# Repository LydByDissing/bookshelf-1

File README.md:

# Bookshelf 1

This is a simply bookshelf speaker, based on a COAX driver from SB Acoustics. The cabinet are a bass reflex cabinet to increase the bass response.

## License
This project and all it's work are licensed under the [CERN Open Hardware Licence Version 2](https://ohwr.org/project/cernohl/wikis/Documents/CERN-OHL-version-2) license.

## Design goals

Initial design goals for this bookshelf speaker:

* Use a COAX driver for optimal timing between drivers
* Compact cabinet
* In room bass extention into the 40Hz range

## Current progress

Prototype cabinet have been designed and built. Initial measurements are been captured. Find them under the [measurements](measurements) folder.

Working on the finishing of the cabinet. Going with a painted finish and initially no driver cover.

An initial crossover have been designed, based on the captured measurements. I'm going for a 2nd order series filter. Currently it looks as depicted below.

The currently simulated results of the speaker + filter looks like this. This result will need to be confirmed by a measurement once the components have arrived.

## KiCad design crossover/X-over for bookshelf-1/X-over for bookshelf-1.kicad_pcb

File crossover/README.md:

# Crossover

The crossover have been simulated and modelled in XSim. The [XSim project file](2-way_LR_eries.dxo) contains the filter simulation.
The measurements used doesn't include impendance measurements.

We are going for a crossover frequence of around 2500Hz. This to keep a reasonable wide dispersion.

As seen in the driver measurements the bass driver has various issues above the crossover frequency wich require us to ensure that these are lowered enough, to not make an audible impact in the tweeter section.

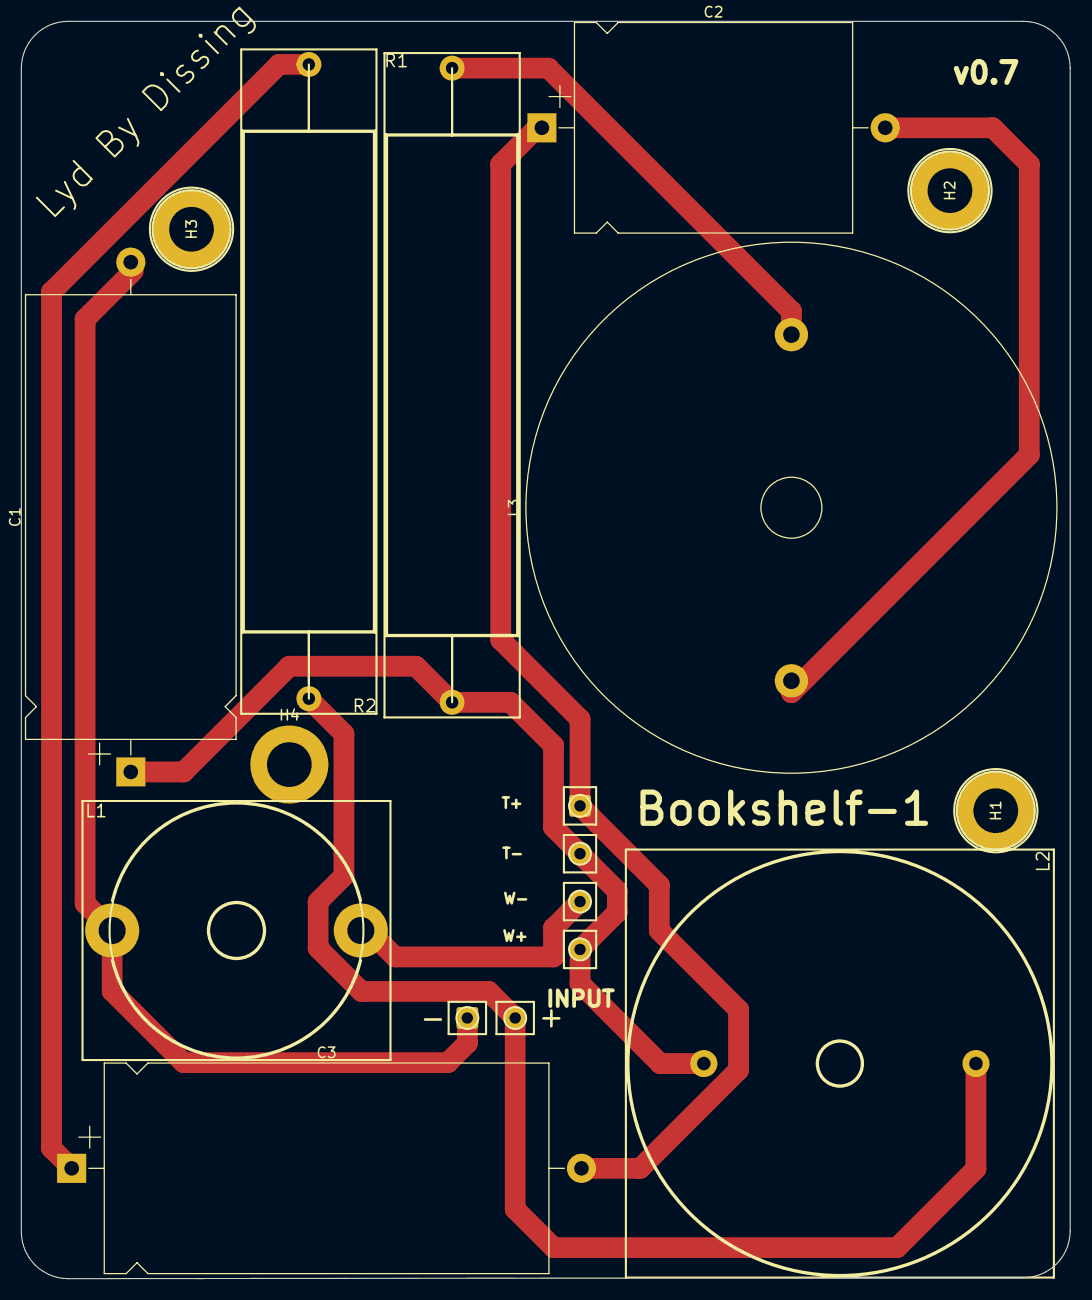
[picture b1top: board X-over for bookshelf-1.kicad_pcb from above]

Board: 2 copper layers, 100.8 x 120.9 mm, 14 parts (0 on the bottom side), 8 nets.

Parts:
C1: 12µF; CP_Axial_L42.5mm_D20.0mm_P49.00mm_Horizontal
C2: 47µF; CP_Axial_L26.5mm_D20.0mm_P33.00mm_Horizontal
C3: 8µF; CP_Axial_L42.5mm_D20.0mm_P49.00mm_Horizontal
H1, H2, H3, H4: MountingHole; MountingHole_4.3mm_M4_DIN965_Pad
J1: Input; SolderWire-0.5sqmm_1x02_P4.6mm_D0.9mm_OD2.1mm
J2: Output; SolderWire-0.5sqmm_1x04_P4.6mm_D0.9mm_OD2.1mm
L1: 1,5mH; L_Radial_D24.4mm_P23.90mm_Murata_1400series
L2: 0,22mH; L_Radial_D40.6mm_P26.16mm_Vishay_IHB-5
L3: 0.1mH; L_Radial_D50.8mm_P33.27mm_Vishay_IHB-6
R1: 1.8Ω; R_Axial_Power_L48.0mm_W12.5mm_P60.96mm
R2: 2,7Ω; R_Axial_Power_L48.0mm_W12.5mm_P60.96mm

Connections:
unnamed: C2.2, L3.1
unnamed: C3.1, R2.2
unnamed: C1.2, J1.1, L1.1
unnamed: J1.2, L2.1, R2.1
unnamed: C2.1, C3.2, J2.1
unnamed: C1.1, J2.2, J2.4, L2.2, R1.2
unnamed: J2.3, L1.2
unnamed: L3.2, R1.1

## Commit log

2023-08-05 Adding mearsurement and simulations results
2023-08-05 Adding documentation
2023-08-05 correction link
2023-08-08 starting to add a sphinx based documentation site
2023-08-08 updating docs on the crossover
2023-08-08 more docs
2023-08-09 cleanup
2023-08-09 adding logo
2023-08-09 moving badge
2023-08-09 removing stuff
2023-08-11 adding iamges
2023-08-12 using white logo
2023-08-12 cleanup + minify
2023-08-12 adding workflows for generating changelog and performing code analysis
2023-08-12 adding changelog
2023-08-12 trying to set github token
2023-08-16 updating doc
2023-08-29 adding x-over KiCAD project for the crossover schematic and PCB design; at least the initial version
2023-08-31 adding KiCAD documents for the XO design
2023-09-13 adding intial work to support PCB draw
2023-09-23 Minimizing overall PCB size
    Now it should both fit inside the cabinet as well as through the driver opening.
2023-09-23 Feature/pcb updates (#3)
    * adding intial work to support PCB draw
    * Minimizing overall PCB size
    Now it should both fit inside the cabinet as well as through the driver opening.
2023-09-23 initial attempt
2023-09-24 Removing all from the failed attempt to add PCB Draw
2023-10-02 Updated schematic and board layout, according to PdB Spec
2023-10-03 Updated schematic and board layout, according to PdB Spec (#4)
2023-10-03 removed unsued stuff
2023-10-03 changing font to roboto
2023-10-04 adding holes
2023-10-04 adding logo as graphic
2024-02-22 making the overall PCB a lot smaller, so it fits through the driver hole
